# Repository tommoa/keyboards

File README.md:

# keyboards

Custom keyboard firmware and hardware, built with Nix.

| Keyboard | Firmware | MCU | Status |
|---|---|---|---|
| Feral (custom split) | ZMK | 2x Seeed XIAO BLE | Making case |
| [Preonic rev3 Drop](https://drop.com/buy/preonic-mechanical-keyboard) | QMK, ZMK | STM32F303 | Retired |

Source lives on [sourcehut](https://git.sr.ht/~tommoa/keyboards),
mirrored to [GitHub](https://github.com/tommoa/keyboards).

## Feral

Custom split keyboard with Choc switches and a 24+2 thumb key layout,
built from an Ergogen PCB design. ZMK firmware with six layers,
home-row mods, and layer-tap keys.

### ConnectPro KVM compatibility

Feral's normal ZMK firmware keeps ZMK's stock combined keyboard and
consumer-control USB HID descriptor so media keys continue to work on
regular hosts. The ConnectPro UDP-12AP DDM keyboard port was more
selective in testing: keyboard typing worked through the KVM, but DDM
hotkey parsing only worked reliably when the keyboard report was exposed
as a dedicated boot-keyboard HID interface.

The `feral-connectpro-zmk` target is the UDP-12AP-compatible firmware. It
builds against the `tommoa/zmk` `usb-hid-device-indexes` branch from
zmkfirmware/zmk#3345 so USB exposes a report-ID-free keyboard HID descriptor
on `HID_0` and consumer/media reports on `HID_1`. This keeps media keys
available while giving the KVM a plain keyboard interface to parse. This
tracks the upstream split-HID support request in
https://github.com/zmkfirmware/zmk/issues/3339.

The relevant HID 1.11 details are:

- Boot-keyboard interfaces use a predefined 8-byte keyboard input report:
  modifiers, a reserved byte, and six key slots. See Appendix B.1
  (Protocol 1: Keyboard) and Appendix F (Legacy Keyboard Implementation).
- If a HID report descriptor uses any report ID, all reports for that HID
  device are prefixed with a report-ID byte. A dedicated single-report
  keyboard HID interface can omit report IDs entirely. See section 5.6
  (Reports) and section 6.2.2.7 (Global Items, `Report ID`).
- USB HID permits both combined report-ID-based descriptors and separate
  HID interfaces. The HID class is defined at the interface level, with
  subclass/protocol fields identifying boot interfaces. See sections 4.2
  (Subclass) and 4.3 (Protocols). Zephyr exposes separate HID instances as
  `HID_0`, `HID_1`, and so on via `CONFIG_USB_HID_DEVICE_COUNT`.

UDP-12AP testing results:

| Change tested | Result |
|---|---|
| Split keyboard `HID_0` and consumer/media `HID_1` | Worked |
| USB boot protocol enabled | Required |
| HKRO with `CONFIG_ZMK_HID_KEYBOARD_REPORT_SIZE=6` | Required |
| NKRO restored | Failed |
| USB boot protocol removed | Failed |
| Full consumer usage reports | Worked |
| `CONFIG_USB_MAX_POWER=250` | Worked |
| Default ZMK sleep behavior | Worked |

The minimal ConnectPro-specific configuration is therefore the split HID
topology plus USB boot protocol and 6KRO/HKRO. Consumer usage narrowing,
USB power reduction, and disabling sleep were not required.

### Keymap

Individual layers:
[QWERTY](https://tommoa.github.io/keyboards/feral-layer-qwerty.svg) |
[Colemak](https://tommoa.github.io/keyboards/feral-layer-colemak.svg) |
[Gaming](https://tommoa.github.io/keyboards/feral-layer-gaming.svg) |
[Q-in-C](https://tommoa.github.io/keyboards/feral-layer-q-in-c.svg) |
[Lower](https://tommoa.github.io/keyboards/feral-layer-lower.svg) |
[Raise](https://tommoa.github.io/keyboards/feral-layer-raise.svg)

## Preonic

5x12 ortholinear with rotary encoder. Both QMK and ZMK firmware share
the same logical keymap: six layers, home-row mods, and layer-tap
keys.

### Layers

| # | Name | Purpose |
|---|------|---------|
| 0 | QWERTY | Default alpha layout |
| 1 | Colemak | Alternative alpha layout |
| 2 | Gaming | Clean QWERTY -- no home-row mods |
| 3 | Qwerty-in-Colemak | QWERTY output when OS is set to Colemak |
| 4 | Lower | Symbols, F-keys, right-hand numpad, media |
| 5 | Raise | Navigation, layer switching, system keys |

<details>
<summary>Preonic keymaps (ASCII)</summary>

#### QWERTY

```
 `      1      2      3      4      5      6      7      8      9      0    Bksp
Tab     Q      W      E      R      T      Y      U      I      O      P   Del/GUI
Esc/Alt A      S    D/Ctl  F/GUI    G      H    J/GUI  K/Ctl    L      ;   '/Alt
Shift   Z      X      C      V      B      N      M      ,      .      /   Ent/Sft
Ctrl   Ctrl   Alt    GUI  Tab/Lwr     Space/Raise x3            Left  Down   Up   Right
```

Hold D for Ctrl, F for GUI, J for GUI, K for Ctrl, Esc for Alt,
' for Alt, Enter for Shift. Tapping term: 175 ms.

#### Lower (symbols + numpad)

```
 ~     F1     F2     F3     F4     F5     F6     F7     F8     F9    F10    F11
 ~      !      @      #      $      %      .      7      8      9          F12
Del     ^      &      *      (      )      -      4      5      6           \
        \      [      ]      {      }      =      1      2      3      =   Next
                                                   0    Mute   Vol-  Vol+  Play
```

#### Raise (navigation + system)

```
Q_in_C QWRTY  Clmk  Game                                                  Boot
                    Bri-  Bri+                   <Tab   Tab>
       Prev   Play  Next              Left   Down    Up  Right
                                      Home   PgDn   PgUp   End             Next
                                              Mute  Vol-  Vol+  Play
```

</details>

### Notable features

- **Home-row mods** on QWERTY, Colemak, and Q-in-C layers. ZMK uses
  separate left/right `balanced` hold-tap behaviors.
- **Layer-tap**: Space activates Raise on hold; Tab activates Lower on
  hold.
- **Rotary encoder**: Page Down / Page Up. QMK also supports Muse mode
  tempo/offset adjustment via the encoder.
- **KVM compatibility**: boots in 6KRO (QMK), USB max power 100 mA,
  console endpoint disabled.
- **Audio** (QMK only): startup song, layer-change songs, NKRO toggle
  chimes, Muse generative music mode, basic MIDI.

### QMK vs ZMK feature gap

Some features exist only in QMK because ZMK lacks the underlying
support:

- Audio / piezo / Muse mode (no ZMK audio driver)
- NKRO toggle (ZMK is compile-time only)
- MIDI
- Persistent default layer (QMK saves to EEPROM)
- `&bootloader` key (broken on STM32F303;
  [ZMK #1086](https://github.com/zmkfirmware/zmk/issues/1086))

## Building

Everything is built with
[Nix flakes](https://zero-to-nix.com/concepts/flakes). No toolchain
installation required.

Flake outputs follow the naming convention `<keyboard>-<firmware>`.

### Firmware builds

```sh
nix build .#preonic-qmk               # Build QMK firmware
nix build .#preonic-zmk               # Build ZMK firmware
nix build .#feral-zmk                 # Build Feral split firmware (zmk_left.uf2 + zmk_right.uf2)
nix build .#feral-connectpro-zmk      # Build Feral ConnectPro split keyboard/consumer USB HID firmware
nix build .#feral-diag-col2row-zmk    # Build Feral bring-up firmware (C2R)
nix build .#feral-raw-scan            # Build standalone Feral raw GPIO scan app (USB serial bitmasks)
```

### Feral hardware and presentation assets

```sh
nix build .#feral-pcb                 # Build Feral Ergogen/KiCad outputs
nix build .#feral-case-shell-stls     # Build shell-only Feral case STLs
nix build .#feral-keymap-assets       # Build slide-ready Feral keymap assets (SVG/YAML/JSON)
```

### Utilities

```sh
nix run .#preonic-qmk-flash           # Build and flash via dfu-util
nix run .#preonic-zmk-update          # Update ZMK west.yml pins + zephyrDepsHash
nix develop                           # QMK dev shell
nix fmt                               # Format Nix + YAML files
```

To enter DFU mode for flashing, double-tap the reset button (or press
the bootloader key on the Raise layer in QMK).

Dependencies are updated automatically on a weekly schedule via GitHub
Actions.

## CI

GitHub Actions builds firmware on every push to `master` and runs
weekly dependency updates for both QMK and ZMK. Feral keymap SVGs are
deployed to [GitHub Pages](https://tommoa.github.io/keyboards/) on
each push. Sourcehut and GitHub are kept in sync bidirectionally.

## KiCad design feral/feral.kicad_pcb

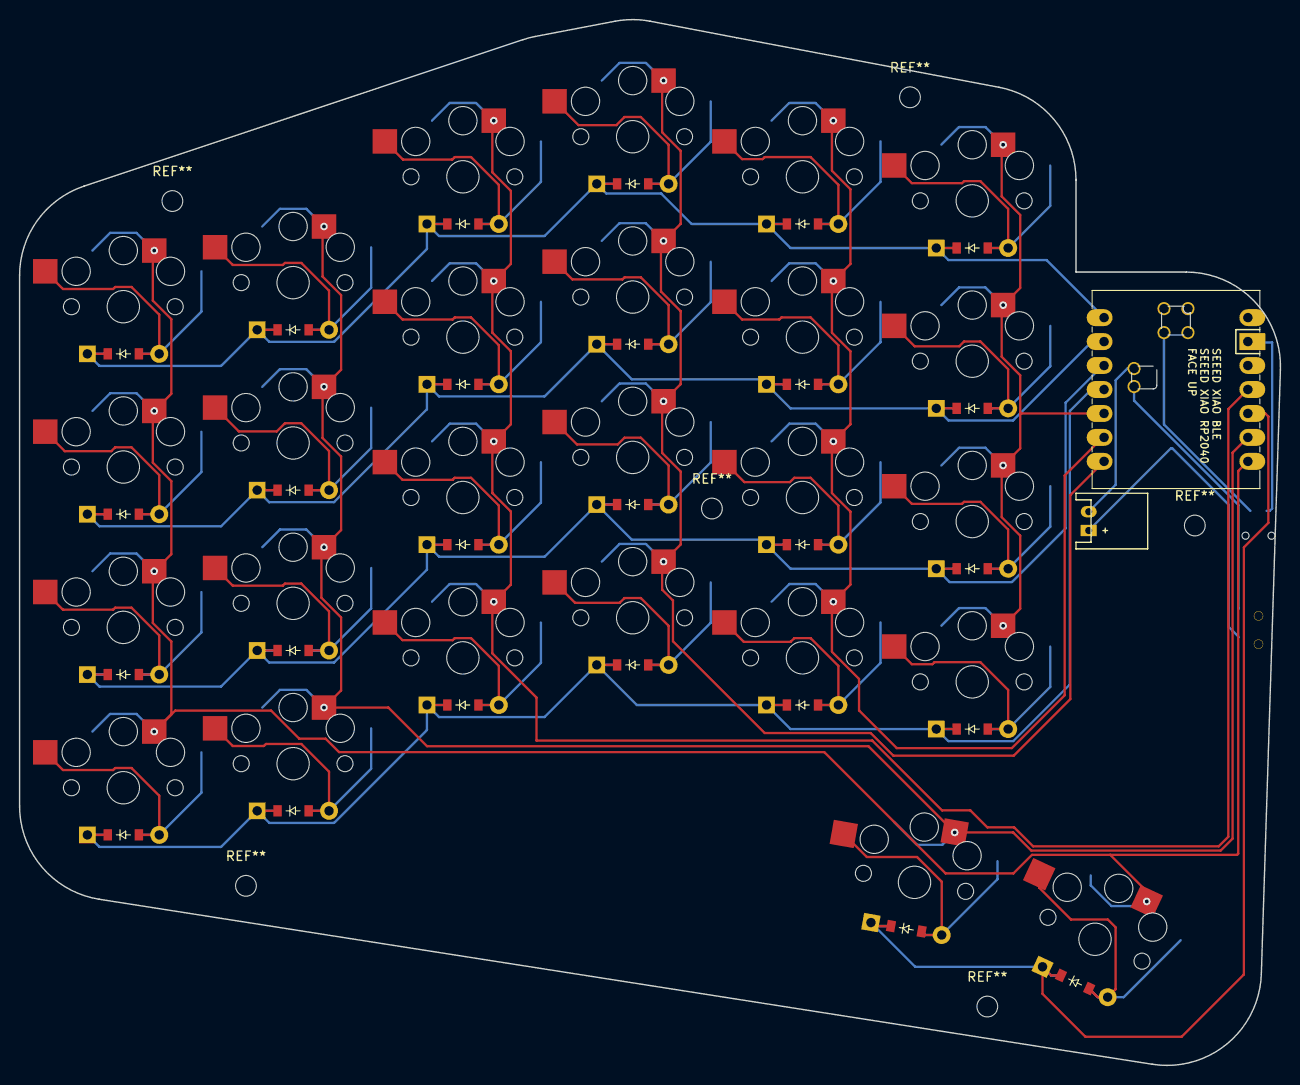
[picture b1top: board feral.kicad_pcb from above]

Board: 2 copper layers, 133.7 x 110.9 mm, 56 parts (1 on the bottom side), 41 nets.

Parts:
B1: Panasonic_EVQPUL_EVQPUC
D1, D2, D3, D4, D5, D6, D7, D8, D9, D10, D11, D12, D13, D14, D15, D16, D17, D18, D19, D20, D21, D22, D23, D24, D25, D26: ComboDiode
JST1: JST_PH_S2B-PH-K_02x2.00mm_Angled
MCU1: xiao-ble
S1, S2, S3, S4, S5, S6, S7, S8, S9, S10, S11, S12, S13, S14, S15, S16, S17, S18, S19, S20, S21, S22, S23, S24, S25, S26: PG1350
T1: SPDT_C128955

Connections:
BAT+: MCU1.19, T1.1
BAT_POS: JST1.1, T1.2
GND: B1.1, JST1.2, MCU1.13, MCU1.20
P0: D4.1, D8.1, D12.1, D16.1, D20.1, D24.1, MCU1.1
P1: D3.1, D7.1, D11.1, D15.1, D19.1, D23.1, MCU1.2
P2: D2.1, D6.1, D10.1, D14.1, D18.1, D22.1, MCU1.3
P3: D1.1, D5.1, D9.1, D13.1, D17.1, D21.1, MCU1.4
P4: MCU1.5, S21.1, S22.1, S23.1, S24.1
P5: MCU1.6, S17.1, S18.1, S19.1, S20.1
P6: MCU1.7, S13.1, S14.1, S15.1, S16.1
P7: MCU1.8, S1.1, S2.1, S3.1, S4.1, S26.1
P8: MCU1.9, S5.1, S6.1, S7.1, S8.1, S25.1
P9: D25.1, D26.1, MCU1.10
P10: MCU1.11, S9.1, S10.1, S11.1, S12.1
RST: B1.2, MCU1.17
index_bottom: D17.2, S17.2
index_home: D18.2, S18.2
index_num: D20.2, S20.2
index_top: D19.2, S19.2
inner_bottom: D21.2, S21.2
inner_home: D22.2, S22.2
inner_num: D24.2, S24.2
inner_top: D23.2, S23.2
middle_bottom: D13.2, S13.2
middle_home: D14.2, S14.2
middle_num: D16.2, S16.2
middle_top: D15.2, S15.2
outer_bottom: D1.2, S1.2
outer_home: D2.2, S2.2
outer_num: D4.2, S4.2
outer_top: D3.2, S3.2
pinky_bottom: D5.2, S5.2
pinky_home: D6.2, S6.2
pinky_num: D8.2, S8.2
pinky_top: D7.2, S7.2
relaxed_thumb: D26.2, S26.2
ring_bottom: D9.2, S9.2
ring_home: D10.2, S10.2
ring_num: D12.2, S12.2
ring_top: D11.2, S11.2
tucked_thumb: D25.2, S25.2

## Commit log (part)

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2025-07-16 feat: First commit
    This is for custom keyboard layouts that I will be making.
2025-07-16 feat: Use qmk-nix-utils instead of rolling own flake.nix
    Currently the upstream is broken, so you'll need to run with:
    ```
    nix build --override-input qmk-nix-utils github:tommoa/qmk-nix-utils
    ```
2025-07-27 fix: Use raw dfu-util command instead of qmk flash
    Directly use dfu-util for flashing instead of qmk flash.
2025-07-27 chore: Remove unneeded files and rename src -> qmk
    I only need the keymap for qmk, and because I plan to eventually add
    zmk/rmk keyboards here as well, it makes sense to refactor so that
    adding them is extremely pain-free.
2025-07-28 feat(feral): Add Nix/Ergogen development environment
2026-02-03 feat(preonic): add brightness, media, and navigation controls to raise/lower layers
    Add comprehensive media, brightness, and navigation controls to both
    function layers for improved productivity.
    Raise layer additions: - Add monitor brightness controls
    (KC_BRID/KC_BRIU) on E/R keys - Add media playback
    (KC_MPRV/KC_MPLY/KC_MNXT) on S/D/F keys - Add vim-style navigation with
    Home on N, PgDn/PgUp under arrow keys, End on . - Add Mute (Left arrow)
2026-02-10 feat(preonic): add KVM compatibility settings
    Some KVM switches can't supply 500mA per USB port and have trouble with
    extra USB endpoints or the startup handshake. This reduces
    USB_MAX_POWER_CONSUMPTION to 100mA (sufficient for a keyboard without
    backlighting), disables the console endpoint, gives the keyboard its own
    dedicated USB endpoint, and skips the USB startup check.
2026-02-10 feat(preonic): add NKRO toggle with audio feedback
    Adds NK_TOGG to the Raise layer so NKRO can be toggled off for KVM
    switches that require 6KRO fallback. Audio chimes provide confirmation:
    an ascending pair when NKRO is enabled and a descending pair when
    switching to 6KRO. NK_ON and NK_OFF also play the corresponding chime.
    The handler runs before process_magic flips keymap_config.nkro, so the
    current state is checked in its pre-toggle form.
2026-02-10 fix(qmk/preonic): use DEL instead of BSLS on Colemak and Q-in-C
    The Colemak and Qwerty-in-Colemak layers had RGUI_T(KC_BSLS) in the
    top-right outer position while QWERTY used RGUI_T(KC_DEL). Standardize
    all base layers to use DEL for consistency.
2026-02-10 chore(flake): rename packages to {board}-{framework} convention
    Expose firmware packages as packages.preonic-qmk and
    packages.preonic-zmk, establishing a naming convention that CI can
    auto-discover via pattern matching on -(qmk|zmk)$. Adding a board only
    requires adding a line to flake.nix.
    The zmk-update app wrapper bakes in UPDATE_NIX_ATTR_PATH and
    UPDATE_WEST_ROOT so nix run .#zmk-update works without callers needing
2026-02-10 feat(ci): add build verification and automated dependency updates
    Add Sourcehut CI build job (.builds/build.yml) that auto-discovers all
    {board}-{framework} packages, builds them, and uploads a firmware.tar.gz
    artifact with .bin and .hex files.
    Add GitHub Actions workflows for bidirectional sync with Sourcehut
    (sync.yml) and weekly automated updates for both ZMK (update-zmk.yml)
    and QMK (update-qmk.yml) dependencies. Update workflows gate on
2026-02-10 fix(ci): replace force-push with rebase in mirror.yml
    The force-push could overwrite commits created by GitHub
    Actions workflows (e.g., automated dependency updates).
    Rebase before pushing so commits from both sides are
    preserved. Falls back to fast-forward-only if the rebase
    fails.
2026-02-10 fix(ci): fix update binary path, push permissions, and separate artifacts
    The zmk-nix update package binary is zmk-firmware-update, not update.
    Fix the wrapper path in flake.nix.
    Add permissions: contents: write to both update workflows so
    github-actions[bot] can push commits to master.
    Rewrite ci.yml with a matrix strategy that auto-discovers firmware
    packages and builds each in parallel with its own named artifact (e.g.,
2026-02-10 fix(flake): correct UPDATE_WEST_ROOT path
    The zmk-nix update script expects west.yml directly inside
    UPDATE_WEST_ROOT. The file is at zmk/preonic/config/west.yml,
    so the path should be zmk/preonic/config, not zmk/preonic.
2026-02-10 fix(flake): include zmk.hex in build output
    The Zephyr build produces both .bin and .hex, but the installPhase only
    copied zmk.bin. Include zmk.hex so CI artifacts contain both formats.
2026-02-10 fix(ci): upload firmware files as individual artifacts
    Upload .bin and .hex as separate named artifacts (e.g., preonic-zmk.bin,
    preonic-zmk.hex) so each file is independently downloadable.
2026-02-10 feat(ci): trigger CI workflow after dependency updates
    Pushes made with the default GITHUB_TOKEN don't trigger
    other workflows. Explicitly dispatch ci.yml after pushing
    update commits so firmware artifacts are built for the
    new dependencies.
2026-02-16 feat(flake): add treefmt-nix auto-formatters
    Both flakes lack any code formatting tooling, making style
    inconsistent across Nix, YAML, and JS files. Integrate
    treefmt-nix into the root and feral flakes to provide a
    unified `nix fmt` command and per-devShell `treefmt` binary.
    The root flake uses nixfmt for Nix files and yamlfmt for YAML.
    The feral sub-flake uses nixfmt and prettier (for JS and YAML).
2026-02-16 fix(qmk/preonic): force 6KRO on boot for KVM compatibility
    The ConnectPro UDP-12AP KVM refuses to enumerate keyboards on its
    dedicated HID port when NKRO is active. NK_TOGG persists its state to
    EEPROM, so accidentally enabling NKRO causes the keyboard to boot in
    NKRO mode on every power cycle, silently breaking KVM detection.
    Add keyboard_post_init_user() to unconditionally disable NKRO after
    EEPROM settings are loaded. The keyboard always starts in 6KRO (boot
2026-02-16 fix(ci): fix workflow_dispatch trigger and zmk-update app reference
    The "Trigger CI" step in both update workflows calls `gh workflow run
    ci.yml`, which requires ci.yml to have a workflow_dispatch trigger. Add
    the missing trigger so the command succeeds instead of exiting with code
    1.
    The treefmt-nix commit (e89f80a) renamed apps.zmk-update to
    apps.preonic-zmk-update in flake.nix but did not update the
2026-02-16 fix(zmk/preonic): use ZMK board variant for preonic
    ZMK PR #3145 (zmkfirmware/zmk@6690d53) restructures all board
    definitions to use HWMv2 board extensions. The bare board ID "preonic"
    resolves to a stock Zephyr board without ZMK-specific NVIC
    configuration, causing a CMSIS build failure:
    cmsis_core_m.h: error: "NUM_IRQ_PRIO_BITS and __NVIC_PRIO_BITS are not
    set to the same value"
2026-02-16 docs: add README and AGENTS.md
    The repository has no documentation for users or AI coding
    agents. Add a README covering the Preonic keymap layout,
    build commands, and CI setup. Add an AGENTS.md with build
    commands, code style guidelines, commit conventions, and
    architecture notes for agent consumption.
    Both files document the naming convention for flake outputs
2026-02-23 zmk: update dependencies
    Automated update of zmk-nix flake input, west.yml pins,
    and zephyrDepsHash.
2026-03-24 feat(qmk/annepro2): add c18 firmware target
    Add a dedicated Anne Pro 2 C18 keymap so the board can be built and
    flashed from the root flake instead of relying on ad hoc QMK commands.
    The layout carries over the Preonic base layers, home-row mods, and
    space-layer behavior while keeping a plain spacebar in gaming mode.
    Pin AnnePro2-Tools in the flake and expose annepro2-qmk and
    annepro2-qmk-flash so builds and IAP flashing follow the same
2026-03-25 docs: clarify feral raw scan usage
    Update the Feral status line to reflect that firmware bring-up is
    finished and the project is in the case-making stage. Expand the README
    and bring-up guide to explain when the raw scan app is useful, so future
    debugging can jump straight to raw matrix bitmasks when the visible
    diagnostic keymap is misleading.
2026-04-09 feat: add feral case CAD workflow
    Track the first printable Feral case as source instead of checked-in
    generated assets. Add the OpenSCAD model, fit-check scripts, and
    supporting docs so the case can be reviewed and regenerated from the PCB
    and layout inputs.
    Make the workflow usable from a clean checkout by documenting the
    regeneration steps, extending the Feral shell for OpenSCAD use, and
2026-04-09 fix(qmk/annepro2): rebalance the raise layer
    Put the C18-specific lighting controls on Raise and move the right GUI
    mod-tap onto the backslash position so the base layer better matches how
    the board is actually used. This keeps the layer focused on board
    controls instead of the older Bluetooth slot arrangement.
2026-04-09 feat(ci): build feral shell STLs from nix
    Stop treating printable Feral shell STLs as tracked artifacts by adding
    a Nix build target that regenerates the shell outputs from the tracked
    KiCad PCB and case sources. This gives CI a single reproducible entry
    point for left/right top and bottom shells and lets the workflow upload
    those artifacts instead of keeping them in git.
    Expose the shell build from the Feral sub-flake and the root flake,
2026-04-09 fix(ci): keep sync dispatch independent of CI trigger
    Automated update workflows already dispatch ci.yml and sync.yml after
    pushing to master, but the default success() step condition let a failed
    CI dispatch block the sourcehut mirror. Gate both dispatches on a
    successful push instead so mirroring still runs when the CI trigger step
    fails.
2026-04-16 fix(feral/case): close the bottom usb-side wall
    The visible opening on the right-bottom shell came from the bottom
    component and XIAO cavities reaching the outer wall near the USB/aux
    area, not from the switch-side relief itself. Constrain those bottom
    cavities to stay inside a printable wall band so the shell closes while
    preserving the intended external openings.
    Add a dedicated checker that exports any bottom-side cavity footprint
2026-04-16 feat(ci): deploy Feral keymap SVGs to GitHub Pages
    The keymap asset build already produced presentation-ready SVGs as CI
    artifacts, but artifacts expire after 90 days and cannot be embedded in
    markdown. Add a deploy-pages job that publishes the SVGs to GitHub Pages
    with a minimal index, giving stable URLs for the README and external
    references.
    Restructure the README to lead with the Feral section and embed the
2026-04-16 fix(ci): drop result/ prefix from Pages site preparation
    The upload-artifact action flattens the result/ symlink, so downloaded
    files land directly in the site directory. Remove the mv/rmdir step that
    assumed a result/ subdirectory.
2026-04-30 feat(zmk/feral): add ConnectPro split HID firmware
    The ConnectPro UDP-12AP DDM parser proved sensitive to ZMK's combined
    USB HID descriptor. A dedicated Feral build applies a local ZMK patch
    that can route keyboard, consumer, and pointing reports to configurable
    Zephyr HID devices while preserving stock combined behavior by default.
    The ConnectPro config places the report-ID-free keyboard descriptor on
    HID_0 and consumer/media reports on HID_1, with USB boot protocol and
2026-04-30 feat(zmk/feral): add split reset firmware
    Feral halves can get stuck with stale split BLE pairing state while host
    profiles should remain intact. This adds dedicated reset firmware that
    clears only the split pairing data for the selected half, plus a full
    settings reset package for cases that need a broader recovery path.
    The reset shields and Nix packages make recovery images buildable
    reproducibly alongside the normal Feral firmware.
